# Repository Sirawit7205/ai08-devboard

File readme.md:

# AI08 Devboard

This is an open-source KiCAD design files for a development for [SAM&WING AI08](https://datasheet.lcsc.com/lcsc/2208221130_Sam-wing-AI08_C521987.pdf) 8-Channel Capacitive Touch Controller IC.

## Pictures

## Features

This devboard provides full flexibility for testing various configurations of the chip and surrounding circuits.

- AI08 Functions
	- Eight 12mm rounded-rectangle touch buttons. (No shield)
	- CSEL pad for sensitivity settings.
- Multiple Outputs
	- 4-bit BCD output (with indicator LEDs)
	- 8-bit decoded output (with indicator LEDs)
	- No Detection and Sleep Calibration indicator LEDs
	- 74HC138 is interchangable for 74HC238 for active-high decoded output.
- Built-In LDO
	- Built-in LDO for better noise reduction.
	- TO-92 and SOT-89 footprints.
	
## Revisions

We are currently at Revision 1. Changelog is below:

**Revision 1 (September 2022)**
 - Initial Design

## What is provided

The goal of this repository is to enable you to build this on your own as easy as possible (although I originally plan to sell this as a kit as well). **The schematics, PCB design, and an interactive BOM is provided.**

Hardware is licensed under `SPDX-License-Identifier: CERN-OHL-S-2.0`

Software is licensed under `SPDX-License-Identifier: GPL` (Actually there is no software for this board. Oops.)

Documentation is licensed under `SPDX-License-Identifier: CC-BY-SA-4.0`

**This project is an OSHWA Certified Open Source Hardware Project with UID [TH000011](https://certification.oshwa.org/th000011.html).**

## Ordering

You can export gerbers from this project and order the board yourself. You can also use the link below to directly order from Aisler.
https://aisler.net/p/NBMILDEY

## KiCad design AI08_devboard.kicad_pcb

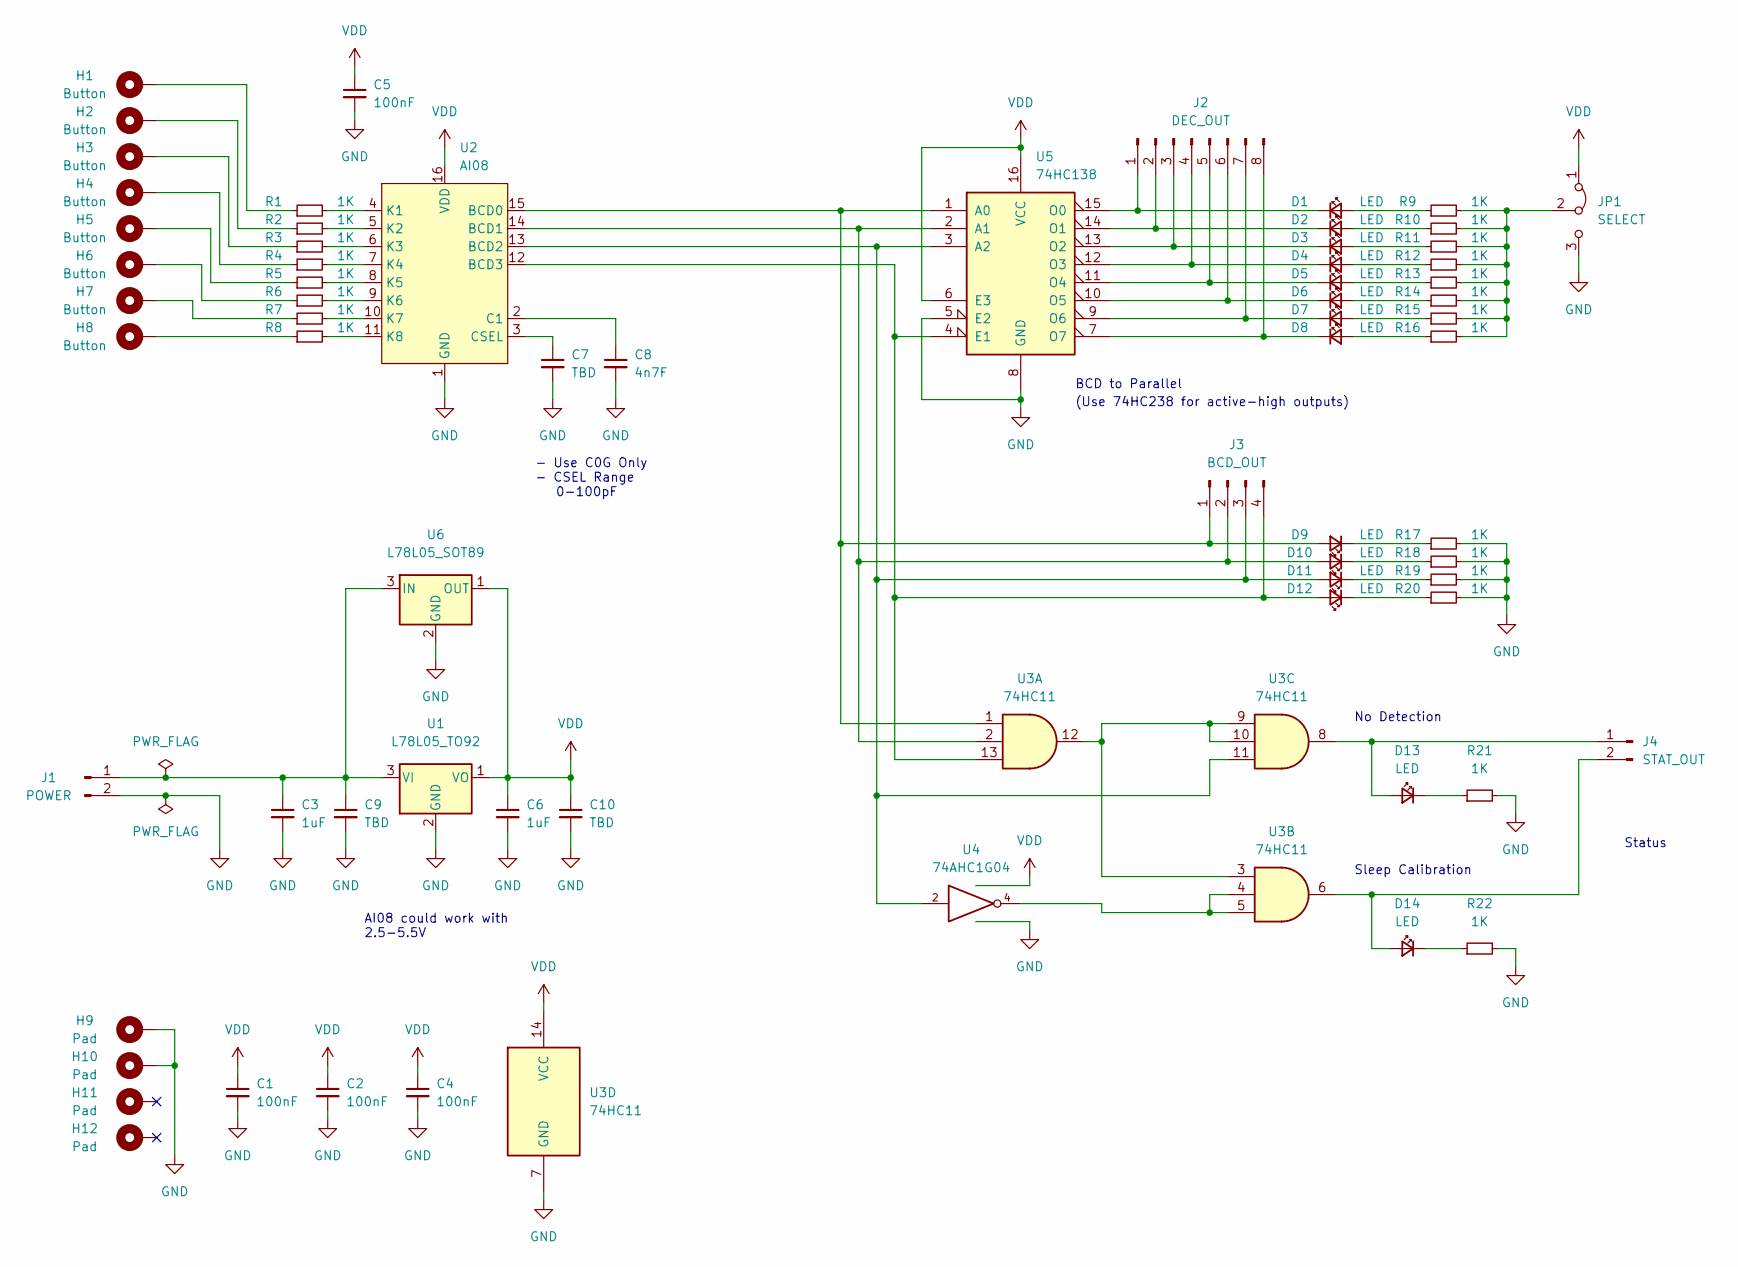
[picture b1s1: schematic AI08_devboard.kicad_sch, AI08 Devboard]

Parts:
C1, C2, C4, C5: 100nF; C_0603_1608Metric
C3, C6: 1uF; C_0805_2012Metric
C7: TBD; C_0603_1608Metric
C8: 4n7F; C_0603_1608Metric
C9, C10: TBD; C_0805_2012Metric
D1, D2, D3, D4, D5, D6, D7, D8, D9, D10, D11, D12, D13, D14: LED; LED_0603_1608Metric
H1, H2, H3, H4, H5, H6, H7, H8: Button; CAPTOUCH_12mm
H9, H10, H11, H12: Pad; MountingHole_2.2mm_M2_DIN965_Pad
J1: POWER; PinHeader_1x02_P2.54mm_Vertical
J2: DEC_OUT; PinHeader_1x08_P2.54mm_Vertical
J3: BCD_OUT; PinHeader_1x04_P2.54mm_Vertical
J4: STAT_OUT; PinHeader_1x02_P2.54mm_Vertical
JP1: SELECT; SolderJumper-3_P1.3mm_Bridged12_Pad1.0x1.5mm
R1, R2, R3, R4, R5, R6, R7, R8, R9, R10, R11, R12, R13, R14, R15, R16, R17, R18, R19, R20, R21, R22: 1K; R_0603_1608Metric
U1: L78L05_TO92; TO-92
U2: AI08; SOIC-16_3.9x9.9mm_P1.27mm
U3: 74HC11; SOIC-14_3.9x8.7mm_P1.27mm
U4: 74AHC1G04; SOT-23-5
U5: 74HC138; SOIC-16_3.9x9.9mm_P1.27mm
U6: L78L05_SOT89; SOT-89-3

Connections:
GND: C1.2, C2.2, C3.2, C4.2, C5.2, C6.2, C7.2, C8.2, C9.2, C10.2, H9.1, H10.1, J1.2, JP1.3 (B), R17.2, R18.2, R19.2, R20.2, R21.2, R22.2, U1.2 (GND), U2.1 (GND), U3.7 (GND), U4.3 (GND), U5.5 (E2), U5.8 (GND), U6.2 (GND)
unnamed: C7.1, U2.3 (CSEL)
unnamed: C8.1, U2.2 (C1)
unnamed: D1.1 (K), J2.1, U5.15 (O0)
unnamed: D1.2 (A), R9.1
unnamed: D2.1 (K), J2.2, U5.14 (O1)
unnamed: D2.2 (A), R10.1
unnamed: D3.1 (K), J2.3, U5.13 (O2)
unnamed: D3.2 (A), R11.1
unnamed: D4.1 (K), J2.4, U5.12 (O3)
unnamed: D4.2 (A), R12.1
unnamed: D5.1 (K), J2.5, U5.11 (O4)
unnamed: D5.2 (A), R13.1
unnamed: D6.1 (K), J2.6, U5.10 (O5)
unnamed: D6.2 (A), R14.1
unnamed: D7.1 (K), J2.7, U5.9 (O6)
unnamed: D7.2 (A), R15.1
unnamed: D8.1 (K), J2.8, U5.7 (O7)
unnamed: D8.2 (A), R16.1
unnamed: D9.1 (K), R17.1
unnamed: D9.2 (A), J3.1, U2.15 (BCD0), U3.1, U5.1 (A0)
unnamed: D10.1 (K), R18.1
unnamed: D10.2 (A), J3.2, U2.14 (BCD1), U3.2, U5.2 (A1)
unnamed: D11.1 (K), R19.1
unnamed: D11.2 (A), J3.3, U2.13 (BCD2), U3.11, U4.2, U5.3 (A2)
unnamed: D12.1 (K), R20.1
unnamed: D12.2 (A), J3.4, U2.12 (BCD3), U3.13, U5.4 (E1)
unnamed: D13.1 (K), R21.1
unnamed: D13.2 (A), J4.1, U3.8
unnamed: D14.1 (K), R22.1
unnamed: D14.2 (A), J4.2, U3.6
unnamed: H1.1, R1.1
unnamed: H2.1, R2.1
unnamed: H3.1, R3.1
unnamed: H4.1, R4.1
unnamed: H5.1, R5.1
unnamed: H6.1, R6.1
unnamed: H7.1, R7.1
unnamed: H8.1, R8.1
unnamed: C3.1, C9.1, J1.1, U1.3 (VI), U6.3 (IN)
unnamed: R1.2, U2.4 (K1)
unnamed: R2.2, U2.5 (K2)
unnamed: R3.2, U2.6 (K3)
unnamed: R4.2, U2.7 (K4)
unnamed: R5.2, U2.8 (K5)
unnamed: R6.2, U2.9 (K6)
unnamed: R7.2, U2.10 (K7)
unnamed: R8.2, U2.11 (K8)
unnamed: JP1.2 (C), R9.2, R10.2, R11.2, R12.2, R13.2, R14.2, R15.2, R16.2
unnamed: U3.4, U3.5, U4.4
unnamed: U3.3, U3.9, U3.10, U3.12
VDD: C1.1, C2.1, C4.1, C5.1, C6.1, C10.1, JP1.1 (A), U1.1 (VO), U2.16 (VDD), U3.14 (VCC), U4.5 (VCC), U5.6 (E3), U5.16 (VCC), U6.1 (OUT)

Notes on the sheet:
- Use C0G Only - CSEL Range 0-100pF
No Detection
Status
AI08 could work with 2.5-5.5V
Sleep Calibration
BCD to Parallel
(Use 74HC238 for active-high outputs)

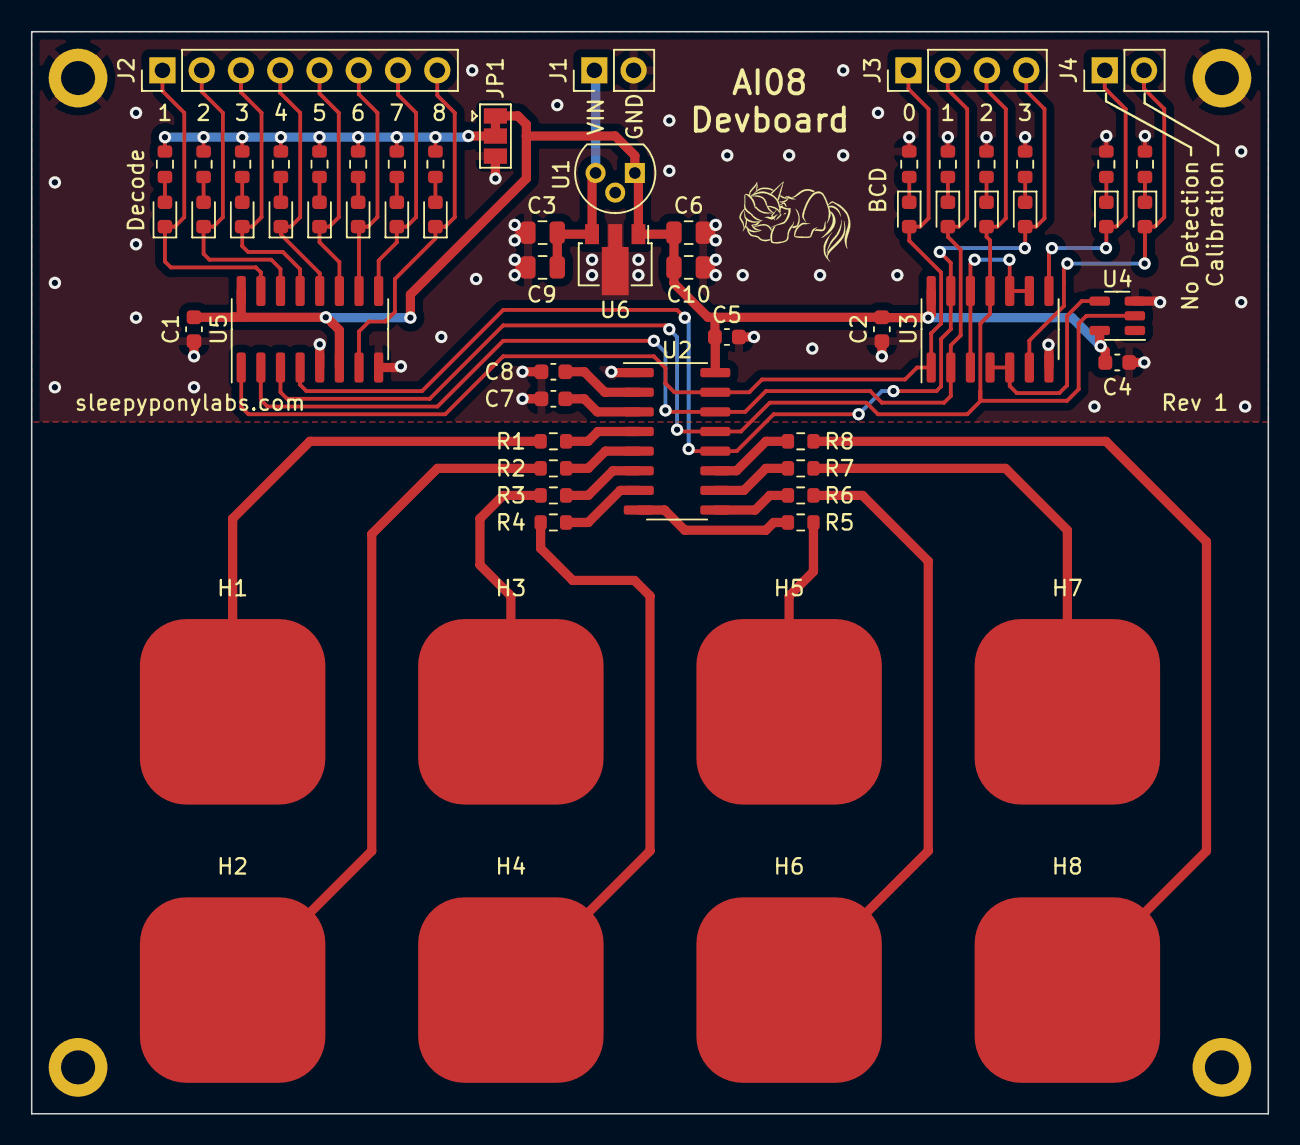
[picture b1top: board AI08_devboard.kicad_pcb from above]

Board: 2 copper layers, 80.0 x 70.0 mm, 69 parts (0 on the bottom side), 52 nets.

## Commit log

2023-05-25 Update readme.md
    Edit licenses and add OSHWA info.
2023-05-28 Update LICENSE
